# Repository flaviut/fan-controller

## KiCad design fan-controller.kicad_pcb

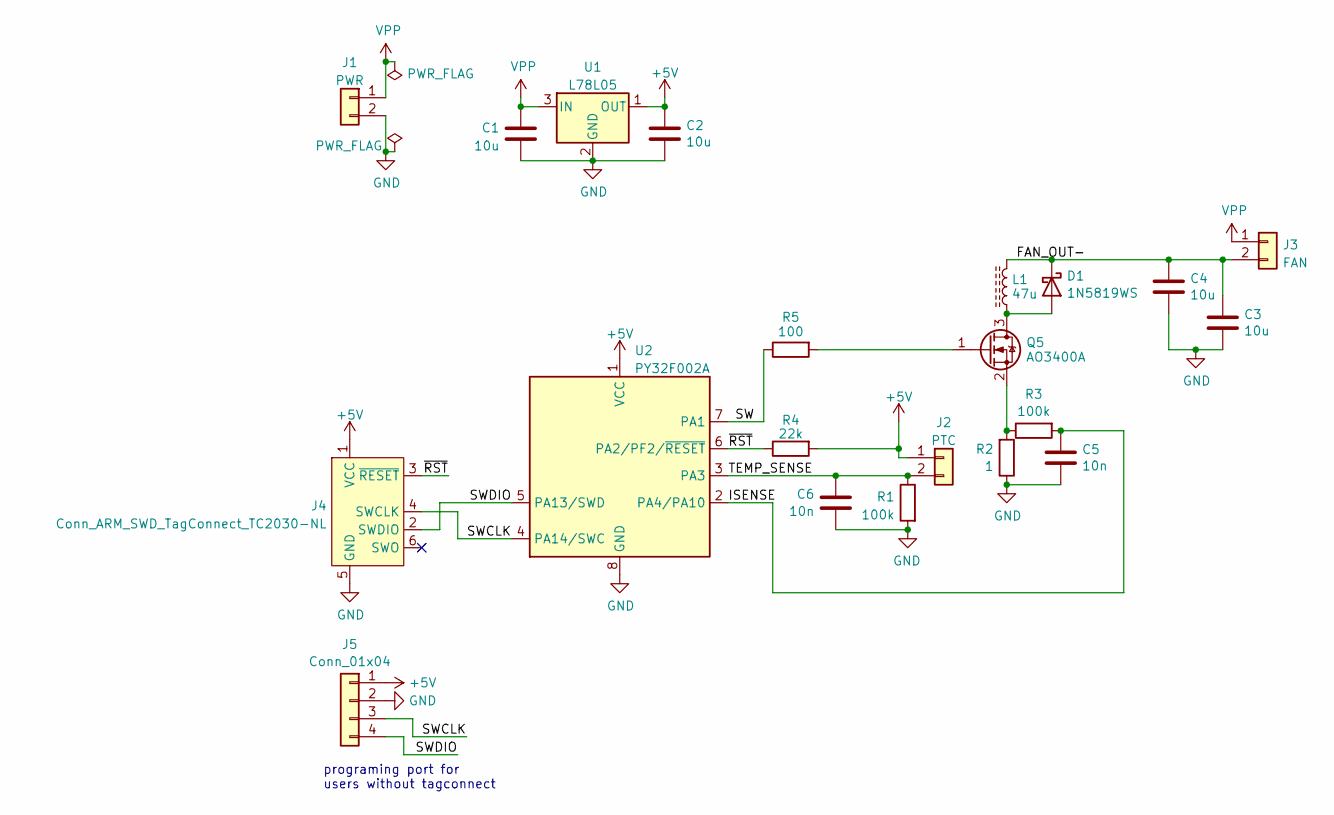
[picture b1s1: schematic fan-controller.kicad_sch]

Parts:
C1, C2, C3, C4: 10u; R_1206_3216Metric; LCSC C13585
C5, C6: 10n; R_0402_1005Metric; LCSC C15195
D1: 1N5819WS; D_SOD-323_HandSoldering; LCSC C191023
J1: PWR; JST_XH_S2B-XH-A_1x02_P2.50mm_Horizontal; LCSC C163035
J2: PTC; JST_XH_S2B-XH-A_1x02_P2.50mm_Horizontal; LCSC C163035
J3: FAN; JST_XH_S2B-XH-A_1x02_P2.50mm_Horizontal; LCSC C163035
J4: Conn_ARM_SWD_TagConnect_TC2030-NL; Tag-Connect_TC2030-IDC-NL_2x03_P1.27mm_Vertical
J5: Conn_01x04; PinHeader_1x04_P2.54mm_Vertical
L1: 47u; L_Abracon_ASPI-4030S; LCSC C54731
Q5: AO3400A; SOT-23; LCSC C20917
R1, R3: 100k; R_0402_1005Metric; LCSC C25741
R2: 1; R_0805_2012Metric; LCSC C25271
R4: 22k; R_0402_1005Metric; LCSC C25768
R5: 100; R_0402_1005Metric; LCSC C25076
U1: L78L05; SOT-89-3; LCSC C71136
U2: PY32F002A; SOIC-8_3.9x4.9mm_P1.27mm; LCSC C5292060

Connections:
+5V: C2.1, J2.1, J4.1 (VCC), J5.1, R4.2, U1.1 (OUT), U2.1 (VCC)
/FAN_OUT-: C3.1, C4.1, D1.1 (K), J3.2, L1.2
/ISENSE: C5.1, R3.2, U2.2 (PA4/PA10)
/SW: R5.1, U2.7 (PA1)
/SWCLK: J4.4 (SWCLK), J5.3, U2.4 (PA14/SWC)
/SWDIO: J4.2 (SWDIO), J5.4, U2.5 (PA13/SWD)
/TEMP_SENSE: C6.1, J2.2, R1.1, U2.3 (PA3)
/~RST: J4.3 (~RESET), R4.1, U2.6 (PA2/PF2/~RESET)
GND: C1.2, C2.2, C3.2, C4.2, C5.2, C6.2, J1.2, J4.5 (GND), J5.2, R1.2, R2.1, U1.2 (GND), U2.8 (GND)
unnamed: D1.2 (A), L1.1, Q5.3 (D)
unnamed: Q5.1 (G), R5.2
unnamed: Q5.2 (S), R2.2, R3.1
VPP: C1.1, J1.1, J3.1, U1.3 (IN)

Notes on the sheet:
programing port for users without tagconnect

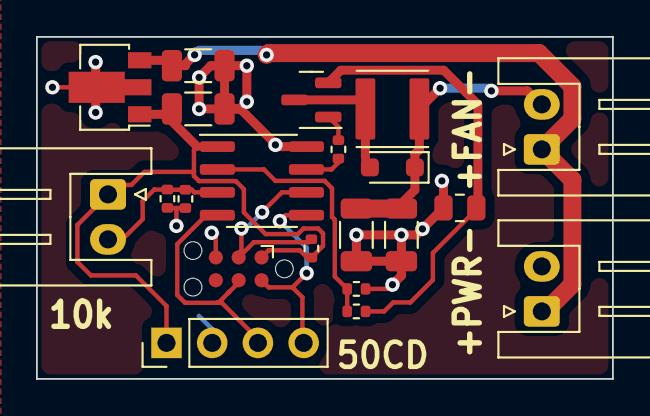
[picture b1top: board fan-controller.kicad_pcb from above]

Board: 2 copper layers, 32.0 x 19.0 mm, 21 parts (0 on the bottom side), 13 nets.

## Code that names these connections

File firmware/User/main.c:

#include "logic.h"
#include "py32f0xx.h"


void SysTick_Handler() {
    HAL_IncTick();
}

void checkOk(int ok) {
    if (ok != HAL_OK) {
        __asm__("bkpt #0");
        while (1) { __NOP(); }
    }
}

static const int SYSCLOCK_FREQ_HZ = (int) 12e6;

static void APP_SystemClockConfig(void) {
    /** use internal oscillator, sysclk = 16MHz */
    checkOk(HAL_RCC_OscConfig(&(RCC_OscInitTypeDef){
        .OscillatorType = RCC_OSCILLATORTYPE_HSI,
        .HSIState = RCC_HSI_ON,
        .HSIDiv = RCC_HSI_DIV2, /* 12MHz */
        .HSICalibrationValue = RCC_HSICALIBRATION_24MHz,
    }));
    // make sure we have a LSI for the watchdog
    checkOk(HAL_RCC_OscConfig(&(RCC_OscInitTypeDef){
        .OscillatorType = RCC_OSCILLATORTYPE_LSI,
        .LSIState = RCC_LSI_ON,
    }));

    checkOk(HAL_RCC_ClockConfig(
        &(RCC_ClkInitTypeDef){
            .ClockType = RCC_CLOCKTYPE_HCLK | RCC_CLOCKTYPE_SYSCLK | RCC_CLOCKTYPE_PCLK1,
            .SYSCLKSource = RCC_SYSCLKSOURCE_HSI, /* SYSCLK source */
            .AHBCLKDivider = RCC_SYSCLK_DIV1,
        },
        FLASH_LATENCY_0));// latency 0 for <= 24MHz
}

// uses LSI clock, 32kHz
IWDG_HandleTypeDef hiwdg = {
    .Instance = IWDG,
    .Init = {
        .Prescaler = IWDG_PRESCALER_256,
        .Reload = 125,// 1s
    },
};

static void APP_Watchdog() {
    checkOk(HAL_IWDG_Init(&hiwdg));
    HAL_IWDG_Refresh(&hiwdg);
}


ADC_HandleTypeDef hadc1 = {
    .Instance = ADC1,
    .Init = (ADC_InitTypeDef){
        .ClockPrescaler = ADC_CLOCK_SYNC_PCLK_DIV4,            /* Analog ADC clock source is PCLK*/
        .Resolution = ADC_RESOLUTION_12B,                      /* conversion resolution 12bit*/
        .DataAlign = ADC_DATAALIGN_RIGHT,                      /* data right alignment */
        .ScanConvMode = ADC_SCAN_DIRECTION_FORWARD,            /* scan sequence direction: up (from channel 0 to channel 11)*/
        .EOCSelection = ADC_EOC_SINGLE_CONV,                   /* ADC_EOC_SINGLE_CONV: single sampling, ADC_EOC_SEQ_CONV: sequence sampling*/
        .LowPowerAutoWait = ENABLE,                            /* ENABLE=After reading the ADC value, start the next conversion , DISABLE=Direct conversion */
        .ContinuousConvMode = DISABLE,                         /* single conversion mode */
        .DiscontinuousConvMode = DISABLE,                      /* Disable discontinuous mode */
        .ExternalTrigConv = ADC_SOFTWARE_START,                /* software trigger */
        .ExternalTrigConvEdge = ADC_EXTERNALTRIGCONVEDGE_NONE, /* No trigger edge */
        .Overrun = ADC_OVR_DATA_OVERWRITTEN,                   /* ADC_OVR_DATA_OVERWRITTEN=overrun when overloaded, ADC_OVR_DATA_PRESERVED=keep old value*/
        .SamplingTimeCommon = ADC_SAMPLETIME_239CYCLES_5,      /* channel sampling time is 239.5ADC clock cycle */
    },
};

static void APP_AdcConfig(void) {
    __HAL_RCC_ADC_FORCE_RESET();
    __HAL_RCC_ADC_RELEASE_RESET(); /* Reset ADC */
    __HAL_RCC_ADC_CLK_ENABLE();    /* Enable ADC clock */

    // PA3 is TEMP_SENSE
    HAL_GPIO_Init(
        GPIOA,
        &(GPIO_InitTypeDef){
            .Mode = GPIO_MODE_ANALOG,
            .Pin = GPIO_PIN_3});
    // PA4 is FAN_SENSE
    HAL_GPIO_Init(
        GPIOA,
        &(GPIO_InitTypeDef){
            .Mode = GPIO_MODE_ANALOG,
            .Pin = GPIO_PIN_4});

    checkOk(HAL_ADC_Calibration_Start(&hadc1));
    checkOk(HAL_ADC_Init(&hadc1));
    checkOk(HAL_ADC_ConfigChannel(&hadc1, &(ADC_ChannelConfTypeDef){
                                              .Rank = ADC_RANK_CHANNEL_NUMBER,
                                              .Channel = ADC_CHANNEL_3,
                                          }));
}


static const int PWM_PERIOD = (SYSCLOCK_FREQ_HZ / PWM_FREQ_HZ) - 1;

TIM_HandleTypeDef htim1 = {
    .Instance = TIM1,
    .Init = {
        .Period = PWM_PERIOD,
        .Prescaler = 0,
        .ClockDivision = TIM_CLOCKDIVISION_DIV1,
        .CounterMode = TIM_COUNTERMODE_UP,
        .RepetitionCounter = 0,
        .AutoReloadPreload = TIM_AUTORELOAD_PRELOAD_DISABLE,
    },
};

static void APP_PwmOutConfig() {
    __HAL_RCC_TIM1_CLK_ENABLE();
    __HAL_RCC_GPIOA_CLK_ENABLE();

    // PWM output 200kHz
    // Pin 7, PA1, TIM1_CH4
    HAL_GPIO_Init(
        GPIOA,
        &(GPIO_InitTypeDef){
            .Mode = GPIO_MODE_AF_PP,
            .Pull = GPIO_PULLUP,
            .Speed = GPIO_SPEED_FREQ_HIGH,
            .Pin = GPIO_PIN_1,
            .Alternate = GPIO_AF13_TIM1,
        });

    checkOk(HAL_TIM_Base_Init(&htim1));
    checkOk(HAL_TIM_PWM_ConfigChannel(
        &htim1,
        &(TIM_OC_InitTypeDef){
            .OCMode = TIM_OCMODE_PWM1,
            .OCFastMode = TIM_OCFAST_DISABLE,
            .OCPolarity = TIM_OCPOLARITY_HIGH,
            .OCNPolarity = TIM_OCNPOLARITY_LOW,
            .OCIdleState = TIM_OCIDLESTATE_RESET,
            .OCNIdleState = TIM_OCNIDLESTATE_RESET,
            .Pulse = 0,// duty cycle = 0%
        },
        TIM_CHANNEL_4));
    checkOk(HAL_TIM_PWM_Start(&htim1, TIM_CHANNEL_4));
}

static void setPwmDutyCycle(double dutyCycle) {
    if (dutyCycle < 0.0) {
        dutyCycle = 0.0;
    } else if (dutyCycle > 1.0) {
        dutyCycle = 1.0;
    }
    __HAL_TIM_SET_COMPARE(&htim1, TIM_CHANNEL_4, (uint32_t) (dutyCycle * PWM_PERIOD));
}

typedef struct {
    uint32_t tempCounts;
    uint32_t fanCounts;
} AdcResults;

AdcResults readAdc() {
    checkOk(HAL_ADC_Start(&hadc1));

    uint32_t allTempCounts = 0;
    uint32_t allFanCounts = 0;
    static const int NUM_SAMPLES = 64;
    for (int i = 0; i < NUM_SAMPLES; i++) {
        // 80us/conversion, 10ms total
        checkOk(HAL_ADC_PollForConversion(&hadc1, 1));
        allTempCounts += HAL_ADC_GetValue(&hadc1);
        checkOk(HAL_ADC_PollForConversion(&hadc1, 1));
        allFanCounts += HAL_ADC_GetValue(&hadc1);
    }
    return (AdcResults){
        .tempCounts = allTempCounts / NUM_SAMPLES,
        .fanCounts = allFanCounts / NUM_SAMPLES};
}


int main(void) {
    HAL_Init();
    APP_SystemClockConfig();
    APP_Watchdog();
    APP_AdcConfig();
    APP_PwmOutConfig();
    SystemCoreClockUpdate();

    const Config config = {

        // 25% min works well for 12V fan
        // 4% min works well for 24V fan
        .fanMinDutyCycle = .04,
        .fanMaxDutyCycle = 1.,
        .fanSpinupDutyCycle = 1.,
        .fanSpinupTimeMs = 200,

        // this seems aggressive, but keep in mind the temperature sensor is
        // generally a little bit away from the temperature-generating
        // component, which means that the temperature measured is signficantly
        // cooler
        .tempMinC = 35,
        .tempMaxC = 65,
        .tempHysteresisC = 8,
    };
    const PtcThermistorConfig thermistorConfig = PTC_THERMISTOR_10K_3950;

    State state = {
        .state = FAN_OFF,
        .lastChangeTimeMs = 0,
        .lastFilteredTempC = 25.,
    };

    while (1) {
        uint32_t startTime = HAL_GetTick();
        AdcResults adcResults = readAdc();

        double tempC = tempCountsToC(adcResults.tempCounts, &thermistorConfig);
        double outputRatio = fanVoltageRatio(tempC, HAL_GetTick(), &config, &state);
        double dutyCycle = ratioToDcmBuckDutyCycle(outputRatio);
        setPwmDutyCycle(dutyCycle);

        // 10ms per loop (will mess up at 49-day uptime rollover, but that's ok)
        uint32_t elapsed = HAL_GetTick() - startTime;
        if (elapsed < 10) {
            HAL_Delay(10 - elapsed);
        }
        HAL_IWDG_Refresh(&hiwdg);
    }
}

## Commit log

2023-02-06 Fix ERC
2023-03-10 Final touch-ups
2023-03-29 Fix flyback diode & add output sense
2023-03-29 Add firmware boilerplate
    import from https://github.com/jaydcarlson/py32-template
2023-03-29 Port to linux
2023-03-29 Update gitignore
2023-03-29 Add idea folder
2023-03-29 Add pre-commit
2023-03-29 Update pre-commit
2023-03-29 Tweak schematic
2023-03-29 Switch boilerplate
2023-03-29 hardware bug fixes
2023-03-30 Fix circuit mistakes
2023-03-30 Finish up firmware
2023-04-07 Fix some bugs & add PWM jumper
2023-06-19 Update firmware
2023-06-19 Avoid makefile over-deletions
2023-06-19 Automatically recreate build dir
2023-06-20 Simplify circuit
2023-06-20 Move errno to BSP file
2023-06-20 Avoid erasing flash before writing
    There's already a system to avoid flashing blocks that haven't changed,
    so there's not reason to spend longer unnecessary
2023-07-20 update logic & add tests
2023-07-21 Remove unused variable
2023-07-21 Enable optimization
2023-07-21 Fix dumb errors (wrong part #)
2023-07-21 Update for actual 10k thermistor
2023-08-20 Implement final functionality
2023-08-20 Place PTC configuration in preamble
2023-09-10 Update comments for power
2023-09-13 Increase refresh rate
    Reduces the impact of noise on the results
2023-09-13 Add additional tests for invariants
    And fix bugs when unexpected values showed up
2023-09-13 Improve hardware reliability
    Current sense + low-pass temperature filter at 100Hz cutoff
2023-09-13 Switch to 10k thermistor in hardware
    easier to find, and the on-board resistor is still 100kΩ so power
    consumption is still low
2024-07-13 Reduce spin-up time
2024-07-13 Update LCSC part numbers
2024-07-13 Reduce temperature bounds
